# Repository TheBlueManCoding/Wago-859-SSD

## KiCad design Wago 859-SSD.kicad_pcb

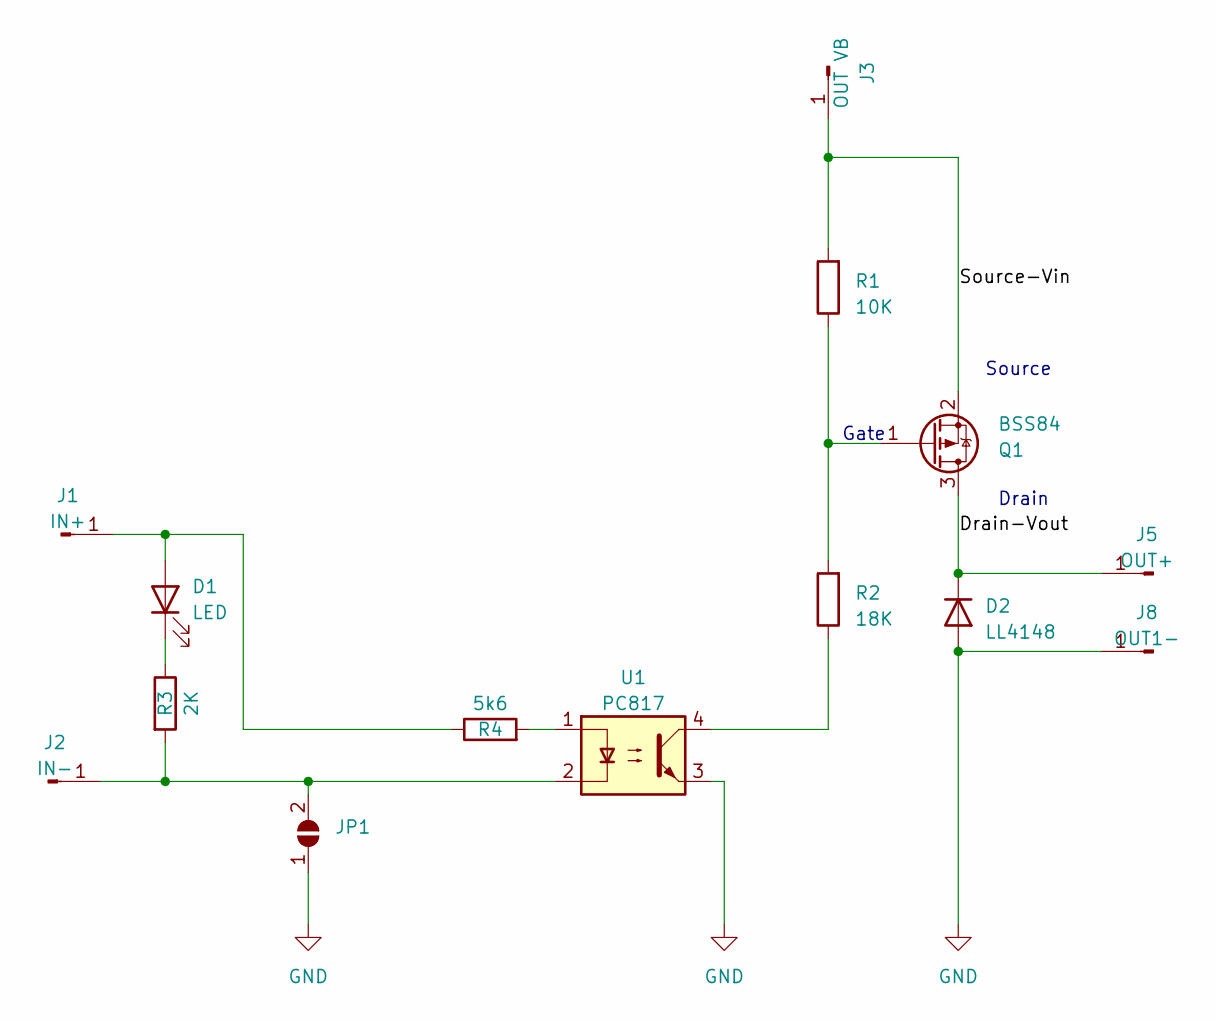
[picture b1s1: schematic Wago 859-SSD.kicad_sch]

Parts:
D1: LED; LED_1206_3216Metric_Pad1.42x1.75mm_HandSolder
D2: LL4148; D_1206_3216Metric_Pad1.42x1.75mm_HandSolder
J1: IN+; Wago_Contact
J2: IN-; Wago_Contact
J3: OUT VB; Wago_Contact
J5: OUT+; Wago_Contact
J8: OUT1-; Wago_Contact
JP1: SolderJumper_2_Open; SolderJumper-2_P1.3mm_Open_Pad1.0x1.5mm
Q1: BSS84; SOT-23_Handsoldering
R1: 10K; R_0805_2012Metric_Pad1.20x1.40mm_HandSolder
R2: 18K; R_0805_2012Metric_Pad1.20x1.40mm_HandSolder
R3: 2K; R_0805_2012Metric_Pad1.20x1.40mm_HandSolder
R4: 5k6; R_0805_2012Metric_Pad1.20x1.40mm_HandSolder
U1: PC817; SMDIP-4_W9.53mm

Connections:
/Drain-Vout: D2.1 (K), J5.1, Q1.3 (D)
/Source-Vin: J3.1, Q1.2 (S), R1.2
GND: D2.2 (A), J8.1, JP1.1 (A), U1.3
unnamed: D1.2 (A), J1.1, R4.1
unnamed: D1.1 (K), R3.1
unnamed: J2.1, JP1.2 (B), R3.2, U1.2
unnamed: Q1.1 (G), R1.1, R2.2
unnamed: R2.1, U1.4
unnamed: R4.2, U1.1

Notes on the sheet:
Drain
Source
Gate

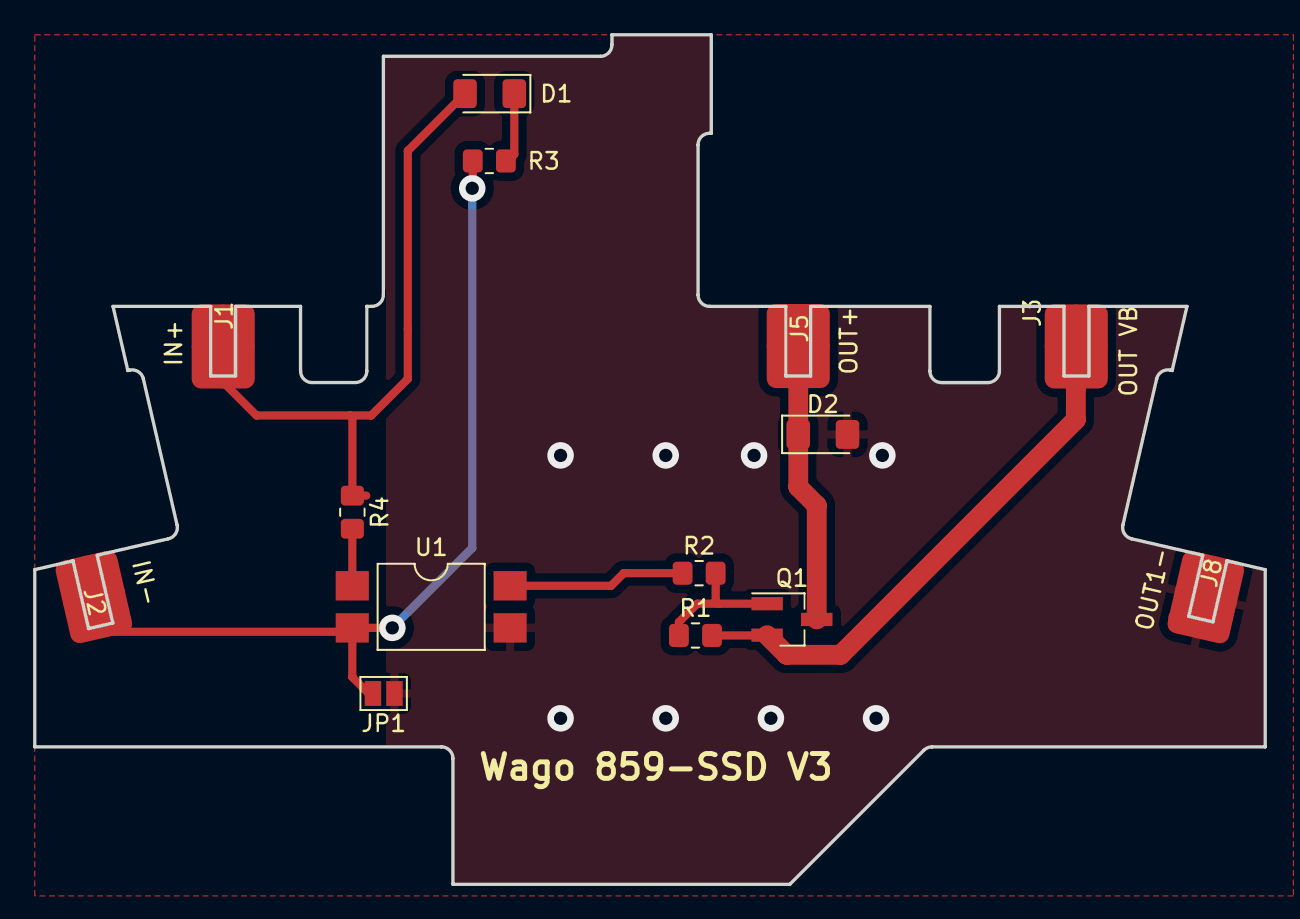
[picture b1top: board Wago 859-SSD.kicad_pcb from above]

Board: 2 copper layers, 74.3 x 51.3 mm, 14 parts (0 on the bottom side), 9 nets.

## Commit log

2023-11-12 WARNING: untested version
2026-06-21 Bugfix Version: V3
